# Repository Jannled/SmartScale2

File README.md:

# SmartScale 2
Modification of a kitchen scale with an ESP32 and a HX711 on a custom PCB. But you can use
this project for other usecases as well, such as measuring the weight of your bee hive, to
measure things you put in your inventory system, to track the weight of the food bowl for
your pets etc.

This project is powered by the amazing [ESP32 SvelteKit](https://github.com/theelims/ESP32-sveltekit) framework.

## Software Features
- Automatic hotspot with captive portal if no WiFi is found
- MQTT with auto discovery for HomeAssistant

> [!NOTE]
> Be sure to select `env:esp32-c6-wroom-1-n4` as the PlatformIO project environment/target
> when using the provided PCB.

## Hardware Features
- HX711 as the loadcell measurement ic with additional filtering
- Builtin battery charger for single cell LiPo batteries with status led
- Powered via USB or battery
- Better power efficiency due to buck switching regulator instead of LDO
- WiFi, Bluetooth and Zigbee compatible due to the ESP32-C6
- touch ic for one button
- easily expandable with qwiic connector (I²C)
- debug with the UART port or the JTAG header
- ESD protection for the USB connector

> [!IMPORTANT]
> The **qwiic and UART** port (J5, J6) have no level shifting and are therefore
> **not 5V tolerant** (3.3V only)!
>
> Also the **battery** connector has **no reverse polarity protection**. Check the pinout of your
> Molex PicoBlade connector (sometimes called JST 1.25 by sketchy online stores) before
> you connect the battery!

You can find the [schematic here](/hardware/SmartScale2-Schematic.pdf)

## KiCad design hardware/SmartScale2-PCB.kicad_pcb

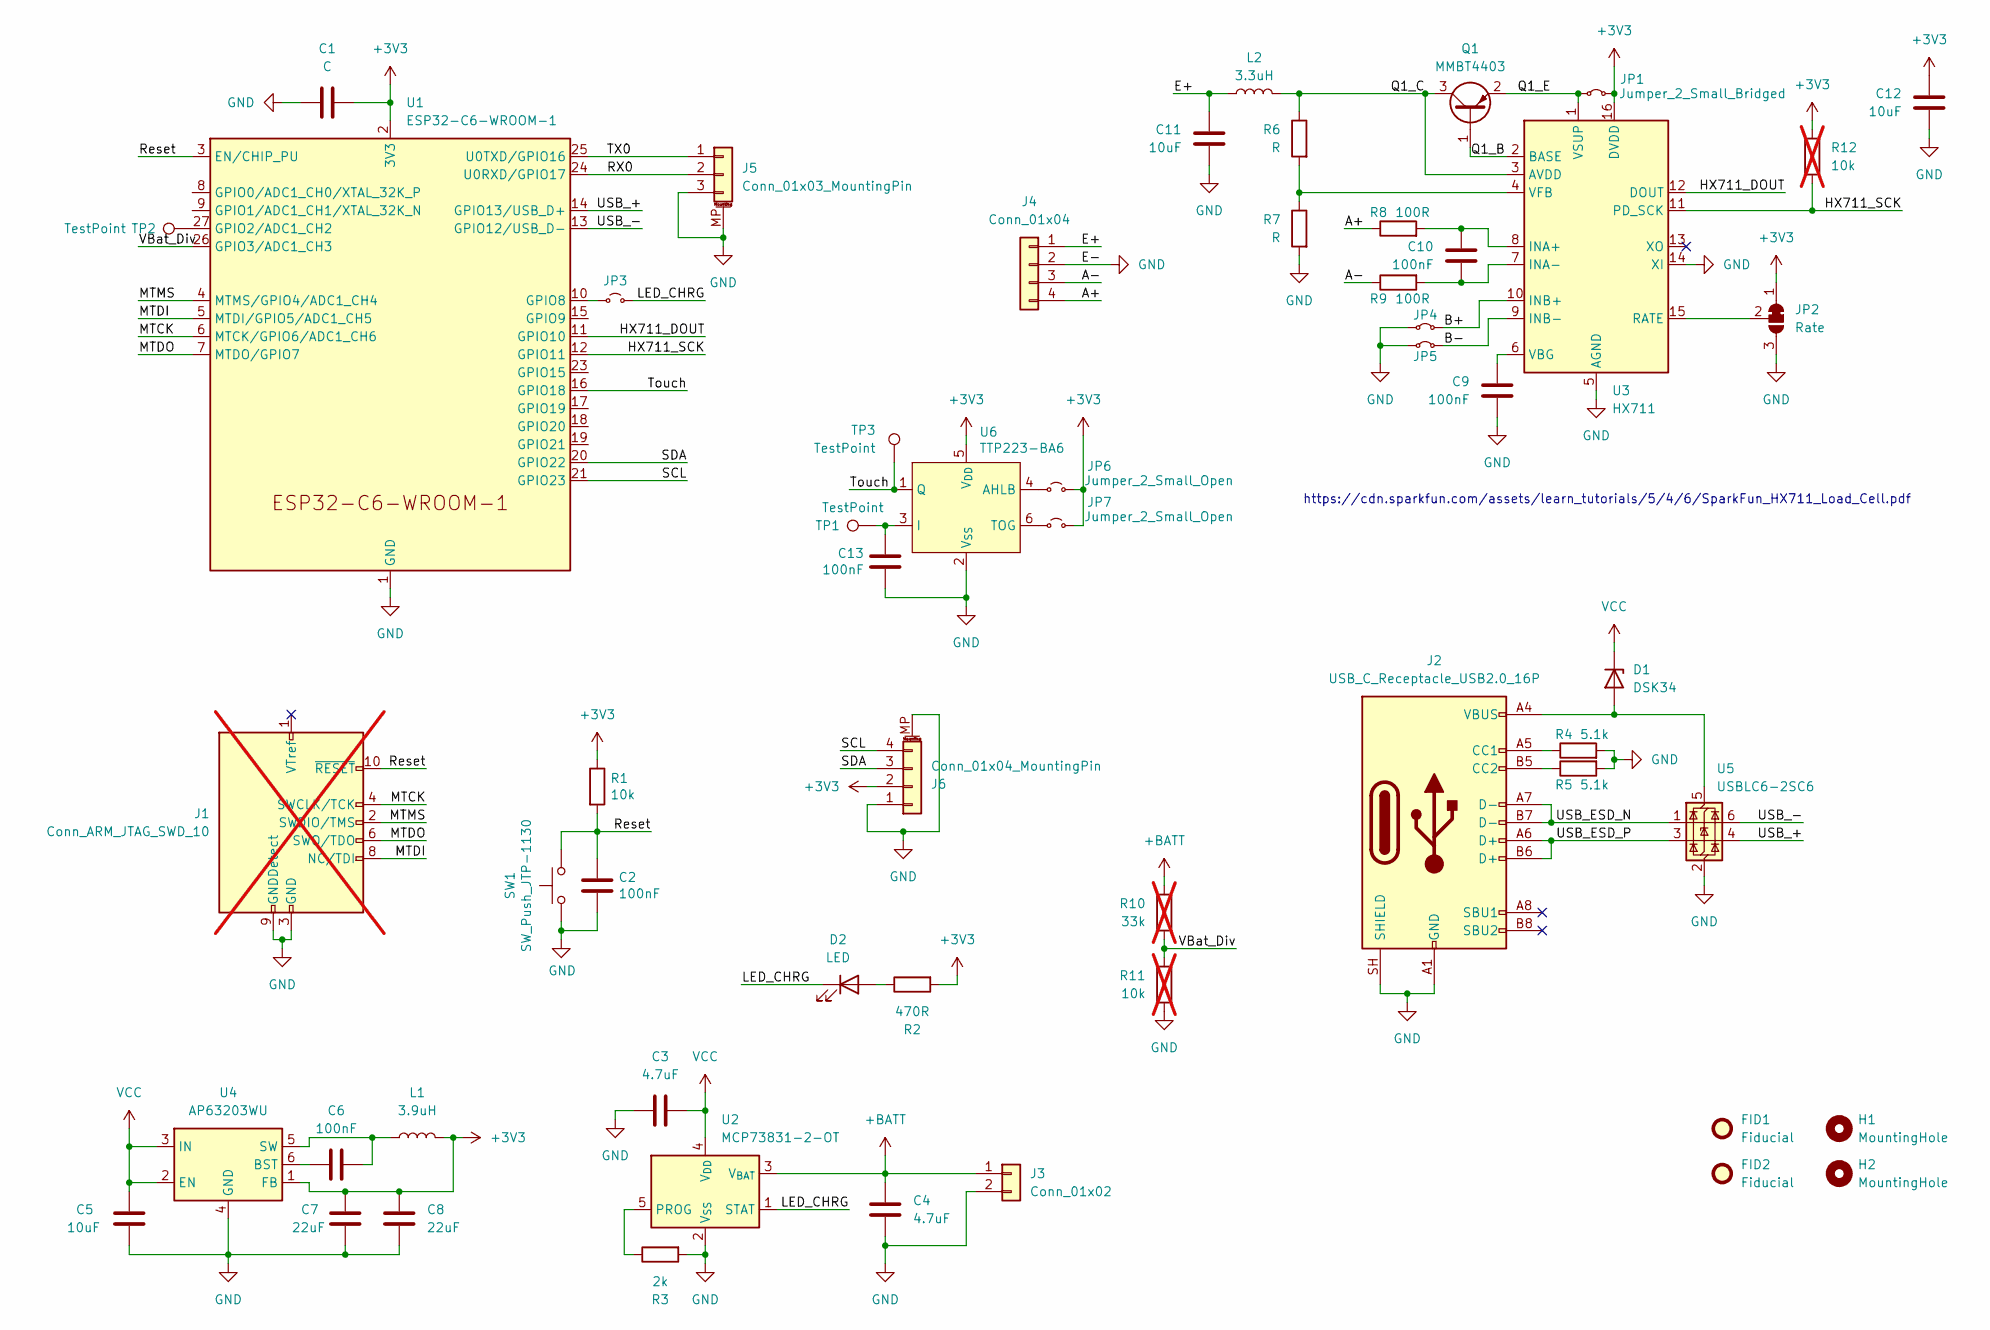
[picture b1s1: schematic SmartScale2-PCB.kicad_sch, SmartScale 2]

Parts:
C1: C; C_0805_2012Metric_Pad1.18x1.45mm_HandSolder
C2, C6, C9, C10, C13: 100nF; C_0805_2012Metric_Pad1.18x1.45mm_HandSolder
C3, C4: 4.7uF; C_0805_2012Metric_Pad1.18x1.45mm_HandSolder
C5, C11, C12: 10uF; C_0805_2012Metric_Pad1.18x1.45mm_HandSolder
C7, C8: 22uF; C_0805_2012Metric_Pad1.18x1.45mm_HandSolder
D1: DSK34; D_SOD-123
D2: LED; LED_0805_2012Metric_Pad1.15x1.40mm_HandSolder
FID1, FID2: Fiducial; Fiducial_0.5mm_Mask1.5mm
H1, H2: MountingHole; MountingHole_3.2mm_M3_DIN965
J1: Conn_ARM_JTAG_SWD_10; PinHeader_2x05_P1.27mm_Vertical_SMD; not fitted
J2: USB_C_Receptacle_USB2.0_16P; USB_C_Receptacle_G-Switch_GT-USB-7010ASV
J3: Conn_01x02; Molex_PicoBlade_53047-0210_1x02_P1.25mm_Vertical
J4: Conn_01x04; PinSocket_1x04_P2.54mm_Vertical
J5: Conn_01x03_MountingPin; JST_SH_SM03B-SRSS-TB_1x03-1MP_P1.00mm_Horizontal
J6: Conn_01x04_MountingPin; JST_SH_SM04B-SRSS-TB_1x04-1MP_P1.00mm_Horizontal
JP1, JP4, JP5: Jumper_2_Small_Bridged; SolderJumper-2_P1.3mm_Bridged_RoundedPad1.0x1.5mm
JP2: Rate; SolderJumper-3_P1.3mm_Bridged12_RoundedPad1.0x1.5mm_NumberL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
JP3, JP6, JP7: Jumper_2_Small_Open; SolderJumper-2_P1.3mm_Open_RoundedPad1.0x1.5mm
L1: 3.9uH; L_Taiyo-Yuden_NR-60xx
L2: 3.3uH; L_0805_2012Metric_Pad1.05x1.20mm_HandSolder
Q1: MMBT4403; SOT-23
R1: 10k; R_0805_2012Metric_Pad1.20x1.40mm_HandSolder
R2: 470R; R_0805_2012Metric_Pad1.20x1.40mm_HandSolder
R3: 2k; R_0805_2012Metric_Pad1.20x1.40mm_HandSolder
R4, R5: 5.1k; R_0805_2012Metric_Pad1.20x1.40mm_HandSolder
R6, R7: R; R_0805_2012Metric_Pad1.20x1.40mm_HandSolder
R8, R9: 100R; R_0805_2012Metric_Pad1.20x1.40mm_HandSolder
R10: 33k; R_0805_2012Metric_Pad1.20x1.40mm_HandSolder; not fitted
R11, R12: 10k; R_0805_2012Metric_Pad1.20x1.40mm_HandSolder; not fitted
SW1: SW_Push_JTP-1130; SW_Push_SPST_NO_Alps_SKRK
TP1: TestPoint; TestPoint_Loop_D2.50mm_Drill1.0mm
TP2, TP3: TestPoint; TestPoint_Pad_D1.0mm
U1: ESP32-C6-WROOM-1
U2: MCP73831-2-OT; SOT-23-5
U3: HX711; SOIC-16_3.9x9.9mm_P1.27mm
U4: AP63203WU; TSOT-23-6
U5: USBLC6-2SC6; SOT-23-6
U6: TTP223-BA6; SOT-23-6

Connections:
+3V3: C1.2, C7.1, C8.1, C12.1, J6.2, JP1.2 (B), JP2.1 (A), JP6.2 (B), JP7.2 (B), L1.2, R1.1, R2.2, R12.1, U1.2 (3V3), U3.16 (DVDD), U4.1 (FB), U6.5 (V_{DD})
+BATT: C4.1, J3.1, R10.1, U2.3 (V_{BAT})
/A+: J4.4, R8.1
/A-: J4.3, R9.1
/B+: JP4.2 (B), U3.10 (INB+)
/B-: JP5.2 (B), U3.9 (INB-)
/E+: C11.1, J4.1, L2.1
/HX711_DOUT: U1.11 (GPIO10), U3.12 (DOUT)
/HX711_SCK: R12.2, U1.12 (GPIO11), U3.11 (PD_SCK)
/LED_CHRG: D2.1 (K), JP3.2 (B), U2.1 (STAT)
/MTCK: J1.4 (SWCLK/TCK), U1.6 (MTCK/GPIO6/ADC1_CH6)
/MTDI: J1.8 (NC/TDI), U1.5 (MTDI/GPIO5/ADC1_CH5)
/MTDO: J1.6 (SWO/TDO), U1.7 (MTDO/GPIO7)
/MTMS: J1.2 (SWDIO/TMS), U1.4 (MTMS/GPIO4/ADC1_CH4)
/Q1_B: Q1.1 (B), U3.2 (BASE)
/Q1_C: L2.2, Q1.3 (C), R6.1, U3.3 (AVDD)
/Q1_E: JP1.1 (A), Q1.2 (E), U3.1 (VSUP)
/RX0: J5.2, U1.24 (U0RXD/GPIO17)
/Reset: C2.1, J1.10 (~RESET), R1.2, SW1.2, U1.3 (EN/CHIP_PU)
/SCL: J6.4, U1.21 (GPIO23)
/SDA: J6.3, U1.20 (GPIO22)
/TX0: J5.1, U1.25 (U0TXD/GPIO16)
/Touch: TP3.1 (1_1), U1.16 (GPIO18), U6.1 (Q)
/USB_+: U1.14 (GPIO13/USB_D+), U5.4 (I/O2)
/USB_-: U1.13 (GPIO12/USB_D-), U5.6 (I/O1)
/USB_ESD_N: J2.A7 (D-), J2.B7 (D-), U5.1 (I/O1)
/USB_ESD_P: J2.A6 (D+), J2.B6 (D+), U5.3 (I/O2)
/VBat_Div: R10.2, R11.1, U1.26 (GPIO3/ADC1_CH3)
GND: C1.1, C2.2, C3.1, C4.2, C5.2, C7.2, C8.2, C9.2, C11.2, C12.2, C13.2, J1.3 (GND), J1.5 (GND), J1.9 (GNDDetect), J2.A1 (GND), J2.A12 (GND), J2.B1 (GND), J2.B12 (GND), J2.SH (SHIELD), J3.2, J4.2, J5.3, J5.MP (MountPin), J6.1, J6.MP (MountPin), JP2.3 (B), JP4.1 (A), JP5.1 (A), R3.2, R4.2, R5.2, R7.2, R11.2, SW1.1, U1.1 (GND), U1.28 (GND), U1.29 (GND), U2.2 (V_{SS}), U3.5 (AGND), U3.14 (XI), U4.4 (GND), U5.2 (GND), U6.2 (V_{SS})
unnamed: D1.2 (A), J2.A4 (VBUS), J2.A9 (VBUS), J2.B4 (VBUS), J2.B9 (VBUS), U5.5 (VBUS)
unnamed: D2.2 (A), R2.1
unnamed: J2.A5 (CC1), R4.1
unnamed: J2.B5 (CC2), R5.1
unnamed: JP2.2 (C), U3.15 (RATE)
unnamed: JP3.1 (A), U1.10 (GPIO8)
unnamed: JP6.1 (A), U6.4 (AHLB)
unnamed: JP7.1 (A), U6.6 (TOG)
unnamed: TP2.1 (1_1), U1.27 (GPIO2/ADC1_CH2)
unnamed: R3.1, U2.5 (PROG)
unnamed: C10.1, R8.2, U3.8 (INA+)
unnamed: C10.2, R9.2, U3.7 (INA-)
unnamed: C9.1, U3.6 (VBG)
unnamed: R6.2, R7.1, U3.4 (VFB)
unnamed: C6.2, U4.6 (BST)
unnamed: C6.1, L1.1, U4.5 (SW)
unnamed: C13.1, TP1.1 (1_1), U6.3 (I)
VCC: C3.2, C5.1, D1.1 (K), U2.4 (V_{DD}), U4.2 (EN), U4.3 (IN)

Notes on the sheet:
https://cdn.sparkfun.com/assets/learn_tutorials/5/4/6/SparkFun_HX711_Load_Cell.pdf

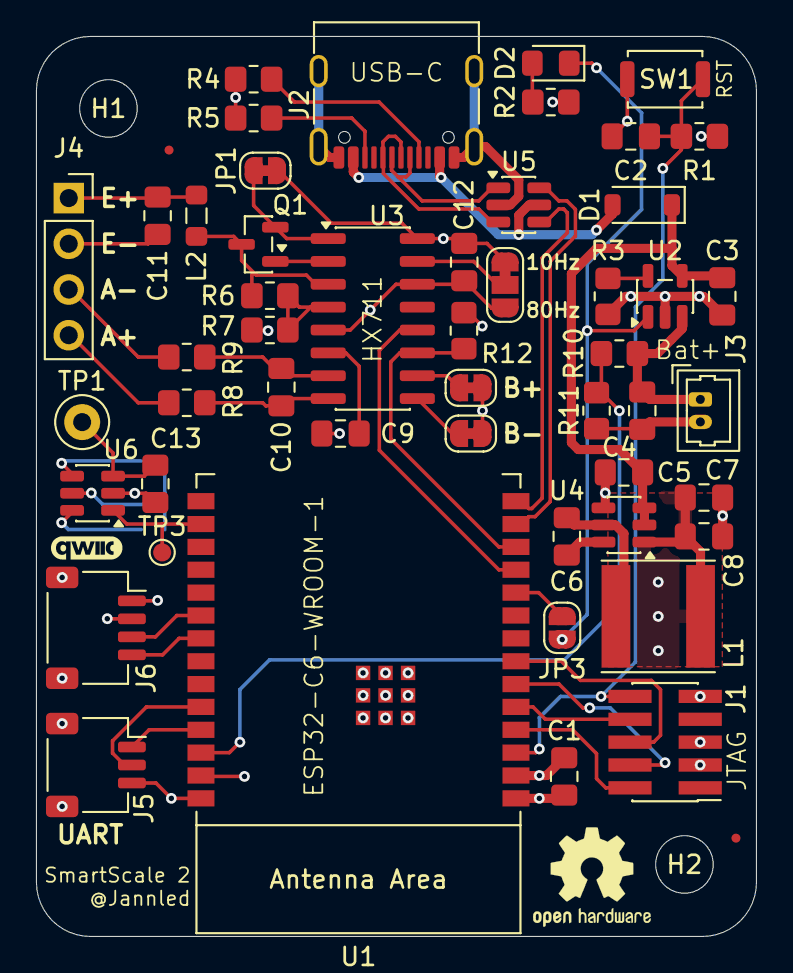
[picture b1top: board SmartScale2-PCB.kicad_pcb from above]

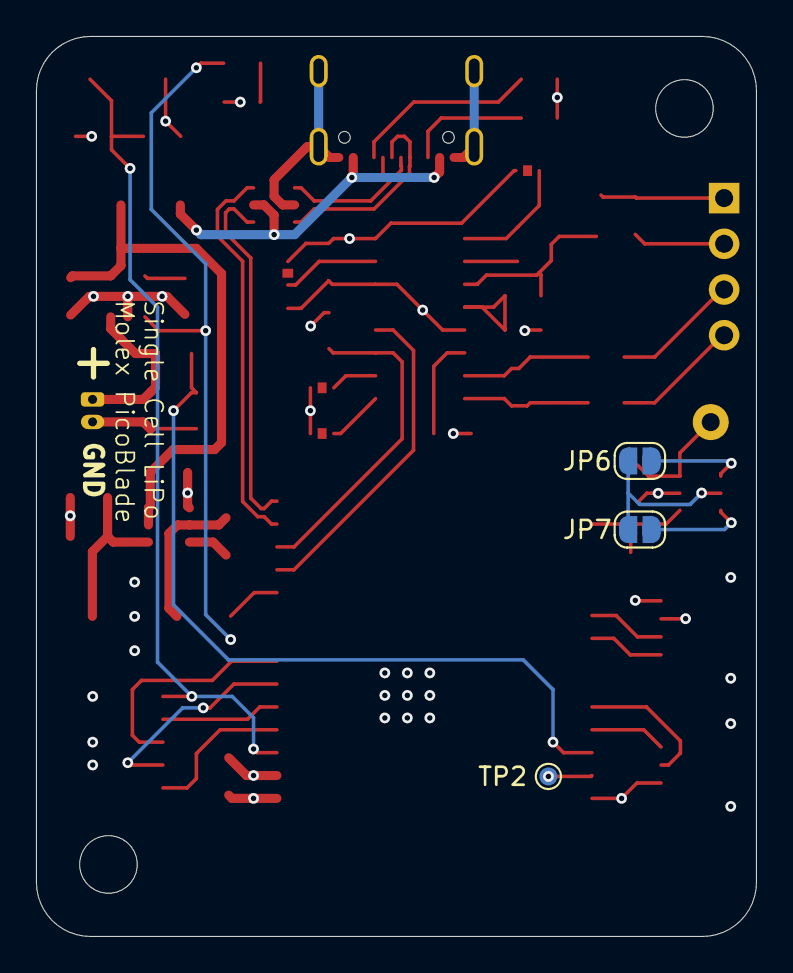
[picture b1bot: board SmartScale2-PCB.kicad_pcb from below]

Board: 4 copper layers, 40.0 x 50.0 mm, 57 parts (3 on the bottom side), 47 nets.

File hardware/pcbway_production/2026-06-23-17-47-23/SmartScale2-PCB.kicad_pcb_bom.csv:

Designator,Quantity,Value,Footprint,Package,MPN,DNP,Mount_Type,Description,KiLib_Generator,Sim.Pins,Sim.Device
C1,1,C,C_0805_2012Metric_Pad1.18x1.45mm_HandSolder,,,,smt,Unpolarized capacitor,,,
"C10, C13, C2, C6, C9",5,100nF,C_0805_2012Metric_Pad1.18x1.45mm_HandSolder,,,,smt,Unpolarized capacitor,SMD_2terminal_chip_molded,,
"C11, C12, C5",3,10uF,C_0805_2012Metric_Pad1.18x1.45mm_HandSolder,,,,smt,Unpolarized capacitor,,,
"C3, C4",2,4.7uF,C_0805_2012Metric_Pad1.18x1.45mm_HandSolder,,,,smt,Unpolarized capacitor,,,
"C7, C8",2,22uF,C_0805_2012Metric_Pad1.18x1.45mm_HandSolder,,,,smt,,,,
D1,1,BZT52C12,D_SOD-123,,,,smt,Zener diode,,,
D2,1,LED,LED_0805_2012Metric_Pad1.15x1.40mm_HandSolder,,,,smt,Light emitting diode,,1=K 2=A,
J1,1,Conn_ARM_JTAG_SWD_10,PinHeader_2x05_P1.27mm_Vertical_SMD,,,Yes,smt,"Cortex Debug Connector, standard ARM Cortex-M SWD and JTAG interface",,,
J2,1,USB_C_Receptacle_USB2.0_16P,USB_C_Receptacle_G-Switch_GT-USB-7010ASV,,,,smt,USB 2.0-only 16P Type-C Receptacle connector,,,
J3,1,Conn_01x02,Molex_PicoBlade_53047-0210_1x02_P1.25mm_Vertical,,,,tht,"Generic connector, single row, 01x02, script generated (kicad-library-utils/schlib/autogen/connector/)",connector/Molex,,
J5,1,Conn_01x03_MountingPin,JST_SH_SM03B-SRSS-TB_1x03-1MP_P1.00mm_Horizontal,,,,smt,"Generic connectable mounting pin connector, single row, 01x03, script generated (kicad-library-utils/schlib/autogen/connector/)",,,
J6,1,Conn_01x04_MountingPin,JST_SH_SM04B-SRSS-TB_1x04-1MP_P1.00mm_Horizontal,,,,smt,"Generic connectable mounting pin connector, single row, 01x04, script generated (kicad-library-utils/schlib/autogen/connector/)",,,
L1,1,3.9uH,L_Taiyo-Yuden_NR-60xx,,,,smt,,,,
L2,1,3.3uH,L_0805_2012Metric_Pad1.05x1.20mm_HandSolder,,,,smt,Inductor,,,
Q1,1,MMBT4403,SOT-23,,,,smt,"PNP transistor, base/emitter/collector",,1=B 2=E 3=C,PNP
R1,1,10k,R_0805_2012Metric_Pad1.20x1.40mm_HandSolder,,,,smt,,,,
R10,1,33k,R_0805_2012Metric_Pad1.20x1.40mm_HandSolder,,,Yes,smt,Resistor,SMD_2terminal_chip_molded,,
R11,1,10k,R_0805_2012Metric_Pad1.20x1.40mm_HandSolder,,,Yes,smt,Resistor,SMD_2terminal_chip_molded,,
R12,1,10k,R_0805_2012Metric_Pad1.20x1.40mm_HandSolder,,,Yes,smt,Resistor,,,
R2,1,470R,R_0805_2012Metric_Pad1.20x1.40mm_HandSolder,,,,smt,Resistor,,,
R3,1,2k,R_0805_2012Metric_Pad1.20x1.40mm_HandSolder,,,,smt,Resistor,,,
"R4, R5",2,5.1k,R_0805_2012Metric_Pad1.20x1.40mm_HandSolder,,,,smt,,SMD_2terminal_chip_molded,,
"R6, R7",2,R,R_0805_2012Metric_Pad1.20x1.40mm_HandSolder,,,,smt,Resistor,,,
"R8, R9",2,100R,R_0805_2012Metric_Pad1.20x1.40mm_HandSolder,,,,smt,Resistor,,,
SW1,1,SW_Push_JTP-1130,SW_Push_SPST_NO_Alps_SKRK,,,,smt,RST,,,
TP1,1,TestPoint,TestPoint_Loop_D2.50mm_Drill1.0mm,,,,tht,test point,,,
U1,1,ESP32-C6-WROOM-1,ESP32-C6-WROOM-1,,,,smt,"ESP32-C6-WROOM-1/U is a module that supports 2.4 GHz Wi-Fi 6 (802.11 ax), Bluetooth® 5 (LE), Zigbee and Thread (802.15.4)",,,
U2,1,MCP73831-2-OT,SOT-23-5,,,,smt,"Single cell, Li-Ion/Li-Po charge management controller, 4.20V, Tri-State Status Output, in SOT23-5 package",,,
U3,1,HX711,SOIC-16_3.9x9.9mm_P1.27mm,,,,smt,"24-bit Analog-to-Digital Converter (ADC) for Weight Scales, SOIC-16 (SOP-16)",,,
U4,1,AP63203WU,TSOT-23-6,,,,smt,,,,
U5,1,USBLC6-2SC6,SOT-23-6,,,,smt,"Very low capacitance ESD protection diode, 2 data-line, SOT-23-6",,,
U6,1,TTP223-BA6,SOT-23-6,,,,smt,,package/gullwing,,

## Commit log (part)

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2026-05-04 Change factory settings
2026-05-08 Add entities and services for a scale
2026-05-10 Wire in Scale service, add HX711 lib
2026-05-11 Got Backend Demo working
2026-05-11 Restructure backend
2026-05-13 Start Frontend work
2026-05-24 Add PCB design files
2026-06-06 PCB rough layout
2026-06-07 Add Touch IC, continue layout
2026-06-10 Push from laptop
2026-06-12 Finish PCB layout
2026-06-15 Change inductor, add pin labels
2026-06-23 Finish PCB
2026-06-24 Investigate 404
2026-06-25 Implement OLED display output
2026-06-26 Add jumpers for touch ic pins, render ui on display
2026-06-26 Add battery connector labels
